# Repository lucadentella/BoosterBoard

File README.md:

# BoosterBoard

BoosterBoard is an opensource board to create a powerful DCC Booster or Command Station.

*BoosterBoard è una scheda opensource disegnata per realizzare un potente Booster DCC o una completa Centralina Digitale.*

## Documentation
 - [Youtube video](https://www.youtube.com/watch?v=jXaGD2t4H4I)
 - [Assembly instructions (*english*)](https://github.com/lucadentella/BoosterBoard/blob/main/documentation/assembly-en.md)
 - [Guide for use as a DCC Booster (*english*)](https://github.com/lucadentella/BoosterBoard/blob/main/documentation/booster-en.md)
 - [Guide for use as a DCC Command Station (*english*)](https://github.com/lucadentella/BoosterBoard/blob/main/documentation/commandstation-en.md)
 
## Documentazione
 - [Video su Youtube](https://www.youtube.com/watch?v=6GtECbDPArw)
 - [Istruzioni per il montaggio (*italiano*)](https://github.com/lucadentella/BoosterBoard/blob/main/documentation/assembly-it.md)
 - [Guida per l'utilizzo come Booster DCC (*italiano*)](https://github.com/lucadentella/BoosterBoard/blob/main/documentation/booster-it.md)
 - [Guida per l'utilizzo come Centralina DCC (*italiano*)](https://github.com/lucadentella/BoosterBoard/blob/main/documentation/commandstation-it.md)

## Technical documents / *Documenti tecnici*
 - [Schematics / *Schema elettrico* (pdf)](https://github.com/lucadentella/BoosterBoard/blob/main/board/BoosterBoard.pdf)
 - [Eagle files](https://github.com/lucadentella/BoosterBoard/tree/main/board)
 - [Part list / *Elenco componenti*](https://github.com/lucadentella/BoosterBoard/blob/main/documentation/partlist.md)

## PCB
PCBs can be ordered directly from PCBWay
*I PCB possono essere ordinati direttamente da PCBWay* 
https://www.pcbway.com/project/shareproject/BoosterBoard.html

## References / *Riferimenti*
 - [A High Power DCC Booster](http://www.trainelectronics.com/DCC_Arduino/DCC_Booster/) (D. Bodnar)
 - [DCC++ BaseStation](https://github.com/DccPlusPlus/BaseStation)

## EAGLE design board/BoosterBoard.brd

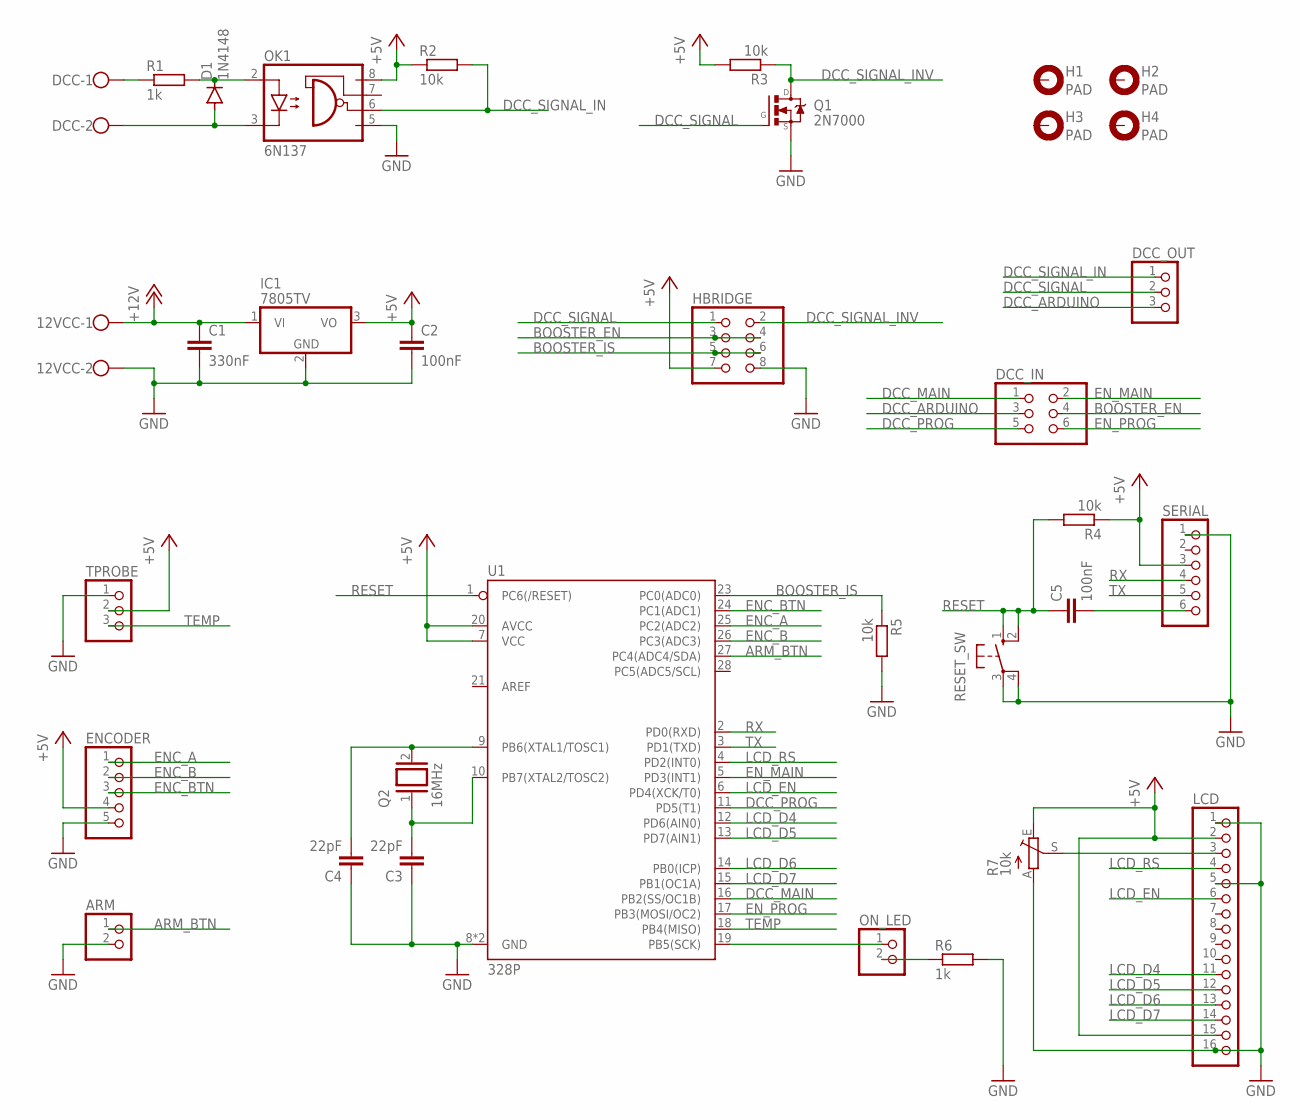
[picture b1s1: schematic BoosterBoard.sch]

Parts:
12VCC: W237-102
ARM: PINHD-1X2; 1X02
C1: 330nF; C050-030X075
C2, C5: 100nF; C050-030X075
C3, C4: 22pF; C025-025X050
D1: 1N4148; DO35-10
DCC: W237-102
DCC_IN: PINHD-2X3; 2X03
DCC_OUT: PINHD-1X3; 1X03
ENCODER: PINHD-1X5; 1X05
H1, H2, H3, H4: PAD; 3,0-PAD
HBRIDGE: PINHD-2X4; 2X04
IC1: 7805TV; TO220V
LCD: PINHD-1X16; 1X16
OK1: 6N137; DIL08
ON_LED: PINHD-1X2; 1X02
Q1: 2N7000; TO-92
Q2: 16MHz; QS
R1, R6: 1k; 0207/2V
R2, R3, R4, R5: 10k; 0207/2V
R7: 10k; B64W
RESET_SW: 10-XX; B3F-10XX
SERIAL: PINHD-1X6; 1X06
TPROBE: PINHD-1X3; 1X03
U1: 328P; DIP28

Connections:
+5V: C2.1, ENCODER.4, HBRIDGE.7, IC1.3 (VO), LCD.2, LCD.15, OK1.8 (VCC), R2.1, R3.2, R4.1, R7.E, SERIAL.3, TPROBE.2, U1.7 (VCC), U1.20 (AVCC)
+12V: 12VCC.1, C1.1, IC1.1 (VI)
ARM_BTN: ARM.1, U1.27 (PC4(ADC4/SDA))
BOOSTER_EN: DCC_IN.4, HBRIDGE.3, HBRIDGE.4
BOOSTER_IS: HBRIDGE.5, HBRIDGE.6, R5.1, U1.23 (PC0(ADC0))
DCC_ARDUINO: DCC_IN.3, DCC_OUT.3
DCC_MAIN: DCC_IN.1, U1.16 (PB2(SS/OC1B))
DCC_PROG: DCC_IN.5, U1.11 (PD5(T1))
DCC_SIGNAL: DCC_OUT.2, HBRIDGE.1, Q1.2 (G)
DCC_SIGNAL_IN: DCC_OUT.1, OK1.6 (VO), R2.2
DCC_SIGNAL_INV: HBRIDGE.2, Q1.3 (D), R3.1
ENC_A: ENCODER.1, U1.25 (PC2(ADC2))
ENC_B: ENCODER.2, U1.26 (PC3(ADC3))
ENC_BTN: ENCODER.3, U1.24 (PC1(ADC1))
EN_MAIN: DCC_IN.2, U1.5 (PD3(INT1))
EN_PROG: DCC_IN.6, U1.17 (PB3(MOSI/OC2))
GND: 12VCC.2, ARM.2, C1.2, C2.2, C3.1, C4.1, ENCODER.5, HBRIDGE.8, IC1.2 (GND), LCD.1, LCD.5, LCD.16, OK1.5 (GND), Q1.1 (S), R5.2, R6.2, R7.A, RESET_SW.3, RESET_SW.4 (P1), SERIAL.1, TPROBE.1, U1.8 (GND), U1.22 (GND)
LCD_D4: LCD.11, U1.12 (PD6(AIN0))
LCD_D5: LCD.12, U1.13 (PD7(AIN1))
LCD_D6: LCD.13, U1.14 (PB0(ICP))
LCD_D7: LCD.14, U1.15 (PB1(OC1A))
LCD_EN: LCD.6, U1.6 (PD4(XCK/T0))
LCD_RS: LCD.4, U1.4 (PD2(INT0))
unnamed: DCC.1, R1.1
unnamed: D1.C, OK1.2 (A), R1.2
unnamed: D1.A, DCC.2, OK1.3 (C)
unnamed: C4.2, Q2.2, U1.9 (PB6(XTAL1/TOSC1))
unnamed: C3.2, Q2.1, U1.10 (PB7(XTAL2/TOSC2))
unnamed: C5.2, SERIAL.6
unnamed: ON_LED.1, U1.19 (PB5(SCK))
unnamed: ON_LED.2, R6.1
unnamed: LCD.3, R7.S
RESET: C5.1, R4.2, RESET_SW.1 (S), RESET_SW.2 (S1), U1.1 (PC6(/RESET))
RX: SERIAL.4, U1.2 (PD0(RXD))
TEMP: TPROBE.3, U1.18 (PB4(MISO))
TX: SERIAL.5, U1.3 (PD1(TXD))

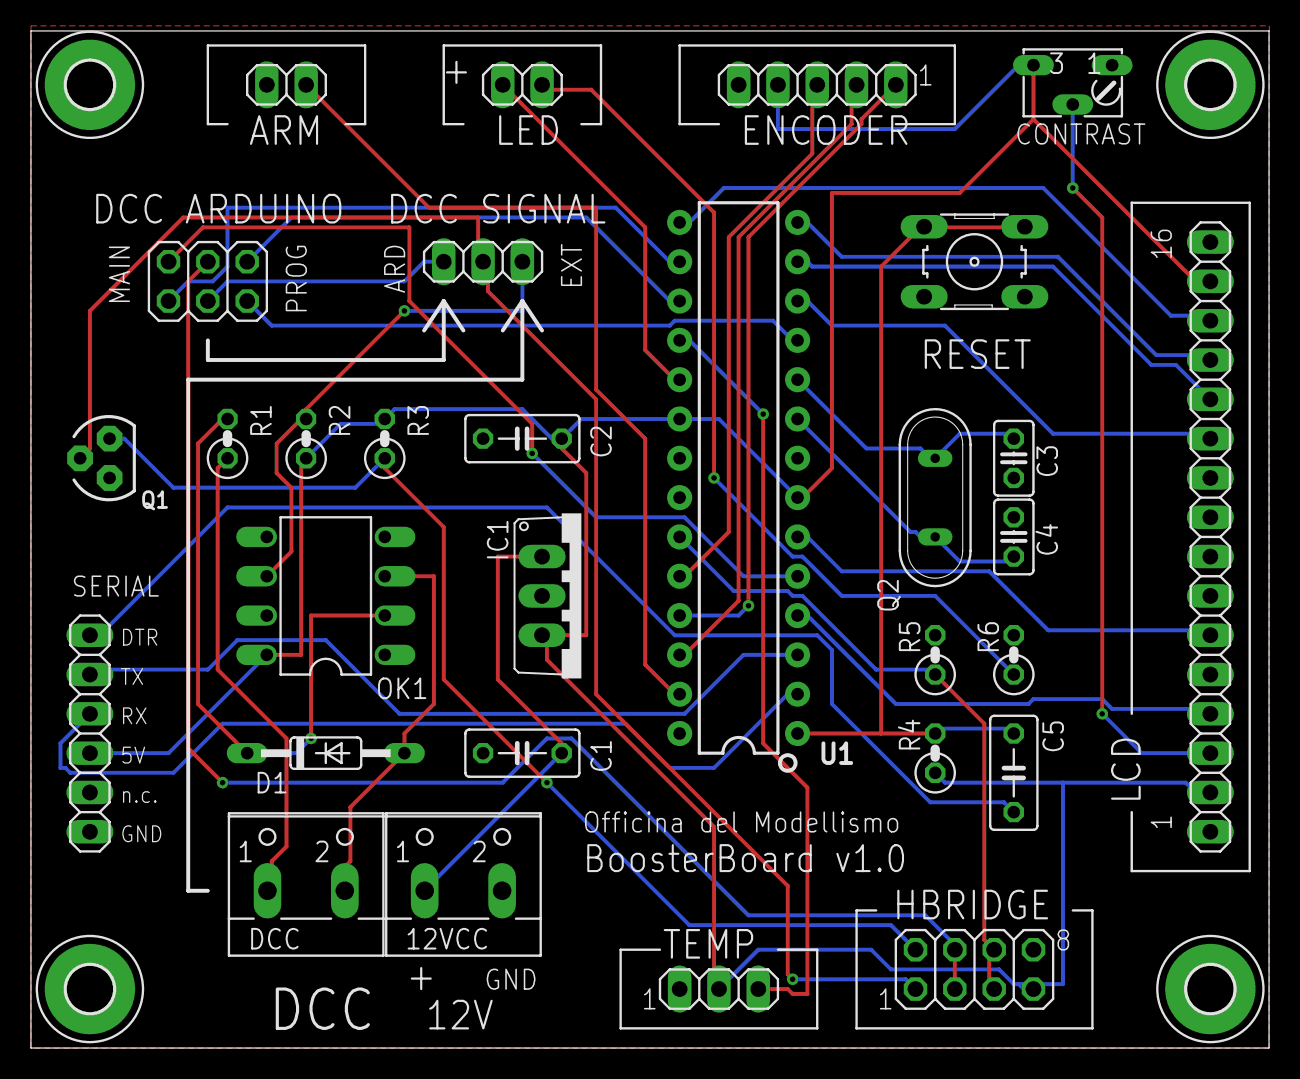
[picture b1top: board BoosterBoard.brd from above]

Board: 2 copper layers, 80.0 x 65.7 mm, 34 parts (0 on the bottom side), 36 nets.

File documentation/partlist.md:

# Part list / *Elenco componenti*
## For the board / Per la scheda
![](https://github.com/lucadentella/BoosterBoard/raw/main/images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
|Name|Description|Value
|--|--|--|
|R1,R6|Resistor 1/4W 1%|1Kohm|
|R2,R3,R4,R5|Resistor 1/4W 1%|10Kohm|
|R7|Variable resistor (RM063)|10Kohm|
|C1|Ceramic capacitor|330nF|
|C2,C5|Ceramic capacitor|100nF|
|C3,C4|Ceramic capacitor|22pF|
|D1|Diode|1N4148|
|Q1|Mosfet|2N7000|
|Q2|Crystal|16MHz|
|U1|Microcontroller|ATmega328p|
|OK1|Optocoupler|6N137|
|IC1|Voltage regulator|L7805|
|RESET_SW|Tactile switch|Omron|
|12VCC,DCC|Terminal block|2P 5mm|
|JMPs|Jumpers|
|ARM,DCC_IN,DCC_OUT...|Pin headers|
## To use as a DCC Booster / Per l'utilizzo come Booster DCC
![](https://github.com/lucadentella/BoosterBoard/raw/main/images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
> Links are for reference only, similar products will work well too / *I link sono forniti solo come riferimento, prodotti simili funzioneranno egualmente bene*

|Name|Description|Link
|--|--|--|
|HBRIDGE|BTS7960B motor driver / *Driver motori BTS7960B*|https://bit.ly/3mZRlfY|
|ARM|Momentary push button / *Pulsante da pannello*|https://bit.ly/2Idf11M|
|LED|LED, choose the color you prefer / *LED, scegli il colore che preferisci*|
|ENCODER|Rotary encoder / *Encoder rotativo*|https://bit.ly/36krh8p
|LCD|16x2 character display / *Display a caratteri 16x2*|https://bit.ly/3lfGiPk
|TEMP|DS18B20 temperature sensor / *Sensore temperatura DS18B20*|https://bit.ly/35dIrFF
## To use as a DCC Command Station / Per l'utilizzo come Centralina DCC
![](https://github.com/lucadentella/BoosterBoard/raw/main/images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
|Name|Description|Link
|--|--|--|
|HBRIDGE|BTS7960B motor driver / *Driver motori BTS7960B*|https://bit.ly/3mZRlfY|
|SERIAL|USB to serial adapter / *Modulo USB - seriale*|https://bit.ly/3eTaGNb

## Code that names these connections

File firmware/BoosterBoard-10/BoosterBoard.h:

#define FIRMWARE_VERSION  "1.0"

// Hardware connections
#define BOOSTER_ENABLE_PIN  3
#define BOOSTER_CURRENT_PIN A0
#define ENCODER_PIN_A       A2
#define ENCODER_PIN_B       A3
#define ENCODER_PIN_BTN     A1
#define ARM_PIN_BTN         A4
#define TEMPERATURE_PIN     12
#define STATUS_LED_PIN      13
#define LCD_RS              2
#define LCD_EN              4
#define LCD_D4              6
#define LCD_D5              7
#define LCD_D6              8
#define LCD_D7              9

// EEPROM addresses
#define E_MAX_CURR_ADDR     0
#define E_MAX_TEMP_ADDR     10
#define E_VALID_VALUES      20

// Absolute maximum values
#define MAX_CURRENT         10.0
#define MAX_TEMPERATURE     80.0

// Sampling parameters
#define CURRENT_SAMPLES       4000
#define TEMPERATURE_WAIT_TIME 1000
#define DEBOUNCE_INTERVAL     50

// FSM
#define W_STOP              0
#define W_POWER             1
#define W_ALERT_CUR         2
#define W_ALERT_TEMP        3
#define W_ALERT_SHORT       4
#define S_IDLE              0
#define S_SELECT            1
#define S_MODIFY            2

// LCD custom chars
byte selectChar[] = {B00000,B00100,B00110,B11111,B00110,B00100,B00000,B00000};
byte modifyChar[] = {B00100,B01110,B11111,B00000,B11111,B01110,B00100,B00000};

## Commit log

2020-11-09 Partlist added
2020-11-09 Schematic in PDF added
2020-11-09 README updated
2020-11-09 Partlist updated
2020-11-09 Partlist updated with jumpers and h-bridge
2020-11-10 Images added
2020-11-10 Images added to documents
2020-11-10 Fix typo
2020-11-10 Images for documentation
2020-11-10 New image
2020-11-10 Assembly instructions added
2020-11-10 README updated with links
2020-11-10 layout fix
2020-11-10 PCBWay link added
2020-11-10 Firmware added
2020-11-10 Eagle files added
2020-11-10 Booster instructions added
2020-11-10 Fix README
2020-11-12 Documentation updated
2020-11-12 fix link
2020-11-14 Youtube links added
2020-11-20 Max current and temperature values fixed
2020-11-20 Improved documentation about h-bridge connections
2025-03-29 Firmware moved to a dedicated folder
2025-03-29 Partlist updated, closes #3

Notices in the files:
parts and their libraries:
SparkFun-IC-Microcontroller: Licensing: Creative Commons ShareAlike 4.0 International - https://creativecommons.org/licenses/by-sa/4.0
